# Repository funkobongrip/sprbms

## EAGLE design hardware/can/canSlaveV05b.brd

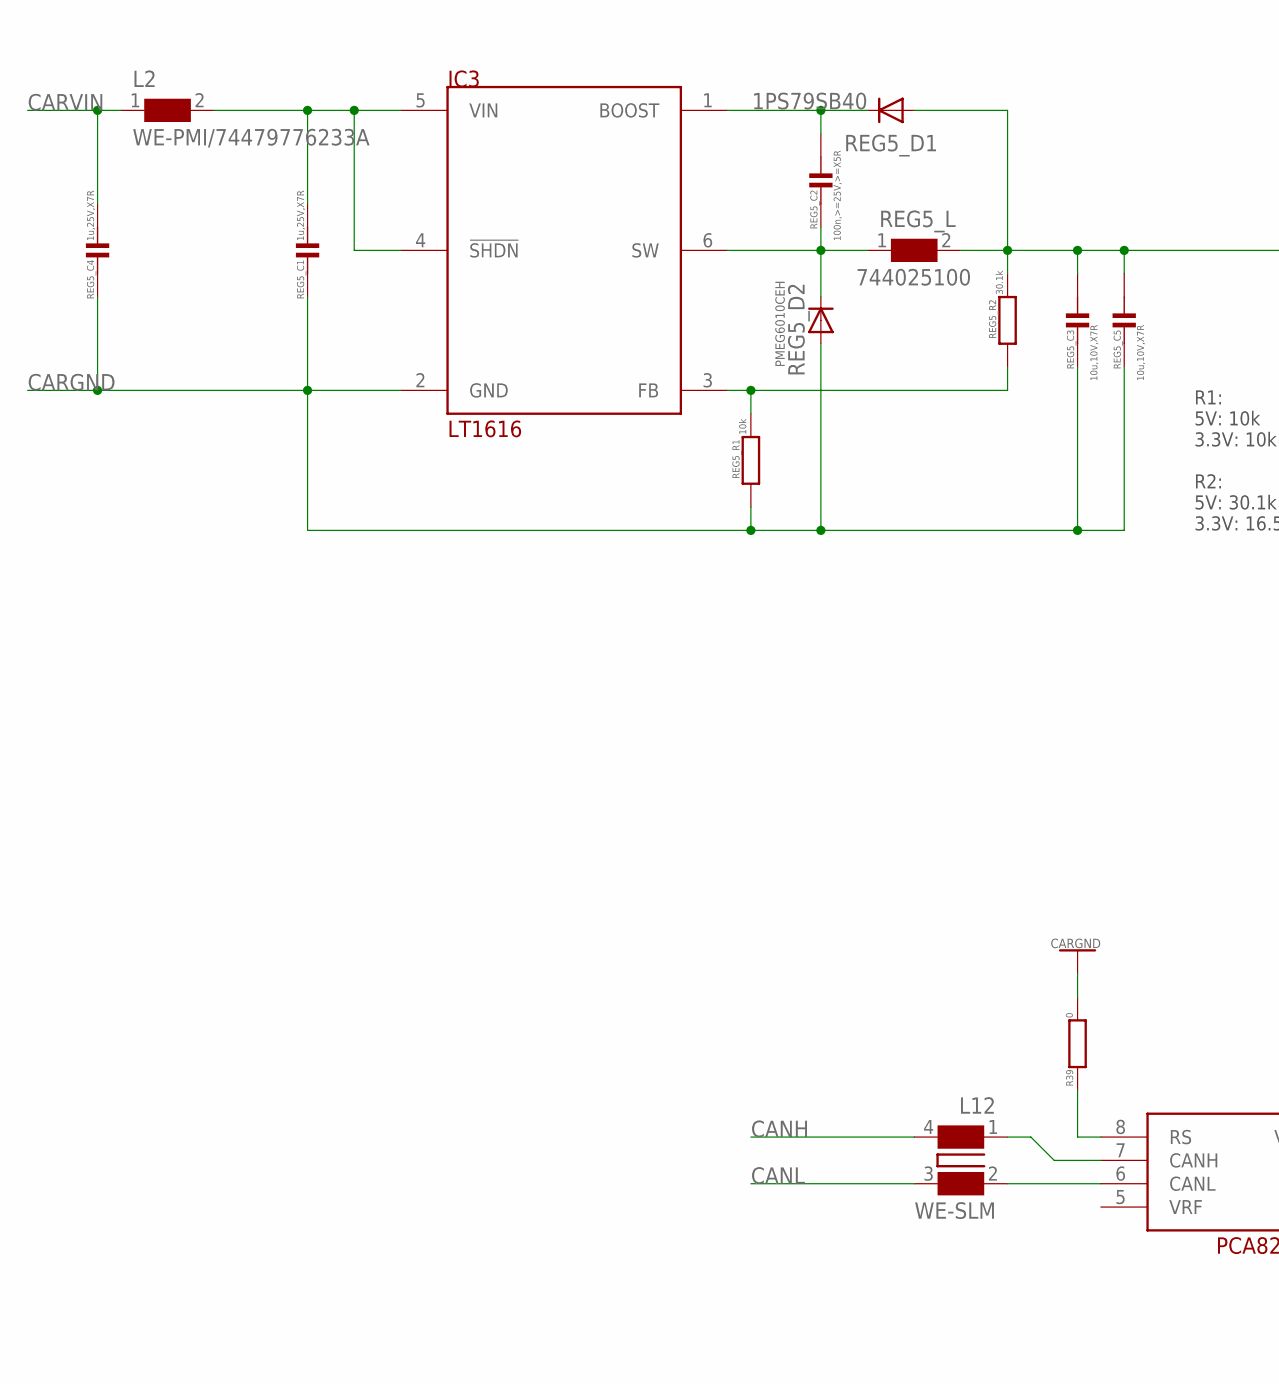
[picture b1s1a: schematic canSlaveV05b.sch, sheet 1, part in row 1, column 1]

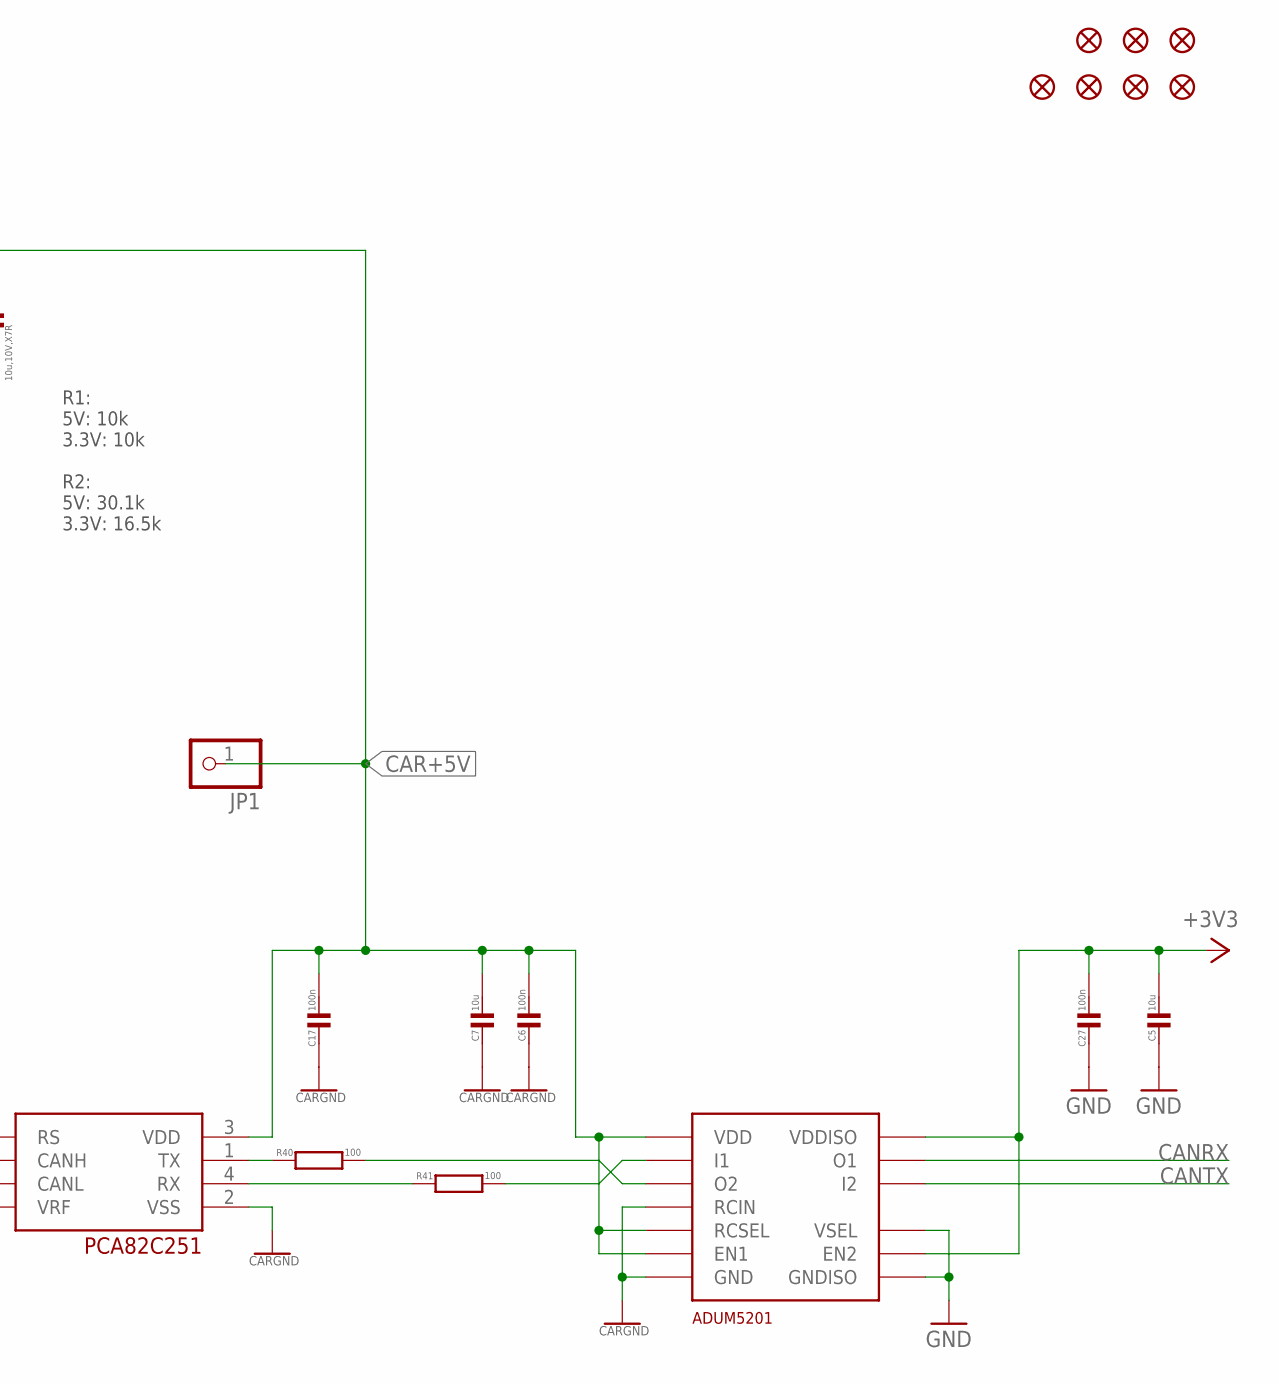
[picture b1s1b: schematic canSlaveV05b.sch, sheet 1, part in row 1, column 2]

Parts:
C5, C7: 10u; C0603
C6, C17, C27: 100n; C0402
FID2, FID3, FID4, FID7, FID8, FID9, FID10: FIDUCIAL""; FIDUCIAL_1MM
IC3: LT1616; SOT23-6
IC5: PCA82C251; SO-8
JP1: PINHD-1X1; 1X01
L2: WE-PMI/74479776233A; WE-PMI_0806
L12: WE-SLM
R39: 0; R0402
R40, R41: 100; R0402
REG5_C1, REG5_C4: 1u,25V,X7R; C0805
REG5_C2: 100n,>=25V,>=X5R; C0402
REG5_C3, REG5_C5: 10u,10V,X7R; C0805
REG5_D1: 1PS79SB40; SOD523
REG5_D2: PMEG6010CEH; SOD123
REG5_L: 744025100; WE-TPC_2828
REG5_R1: 10k; R0402
REG5_R2: 30.1k; R0402
U$2: ADUM5201; SO16WB

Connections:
+3V3: C5.1, C27.1, U$2.P$10 (EN2), U$2.P$16 (VDDISO); also elsewhere on the board
BOOST1: IC3.1 (BOOST), REG5_C2.1, REG5_D1.C
CANH: L12.4; also elsewhere on the board
CANL: L12.3 (2); also elsewhere on the board
CANRX: U$2.P$14 (O1); also elsewhere on the board
CANTX: U$2.P$13 (I2); also elsewhere on the board
CAR+5V: C6.1, C7.1, C17.1, IC5.3 (VDD), JP1.1, REG5_C3.1, REG5_C5.1, REG5_D1.A, REG5_L.2, REG5_R2.2, U$2.P$1 (VDD), U$2.P$6 (RCSEL), U$2.P$7 (EN1)
CARGND: C6.2, C7.2, C17.2, IC3.2 (GND), IC5.2 (VSS), R39.2, REG5_C1.2, REG5_C3.2, REG5_C4.2, REG5_C5.2, REG5_D2.2 (A), REG5_R1.1, U$2.P$2 (GND), U$2.P$5 (RCIN), U$2.P$8 (GND); also elsewhere on the board
CARVIN: L2.1, REG5_C4.1; also elsewhere on the board
CARVINFILT: IC3.4 (!SHDN), IC3.5 (VIN), L2.2, REG5_C1.1
CAR_CANRX: R41.2, U$2.P$3 (I1)
CAR_CANRX_T: IC5.4 (RX), R41.1
CAR_CANTX: R40.2, U$2.P$4 (O2)
CAR_CANTX_T: IC5.1 (TX), R40.1
FB1: IC3.3 (FB), REG5_R1.2, REG5_R2.1
GND: C5.2, C27.2, U$2.P$9 (GNDISO), U$2.P$11 (VSEL), U$2.P$15 (GNDISO); also elsewhere on the board
unnamed: IC5.7 (CANH), L12.1 (3)
unnamed: IC5.6 (CANL), L12.2 (1)
RS1: IC5.8 (RS), R39.1
SW1: IC3.6 (SW), REG5_C2.2, REG5_D2.1 (C), REG5_L.1

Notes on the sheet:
R1: 5V: 10k 3.3V: 10k R2: 5V: 30.1k 3.3V: 16.5k

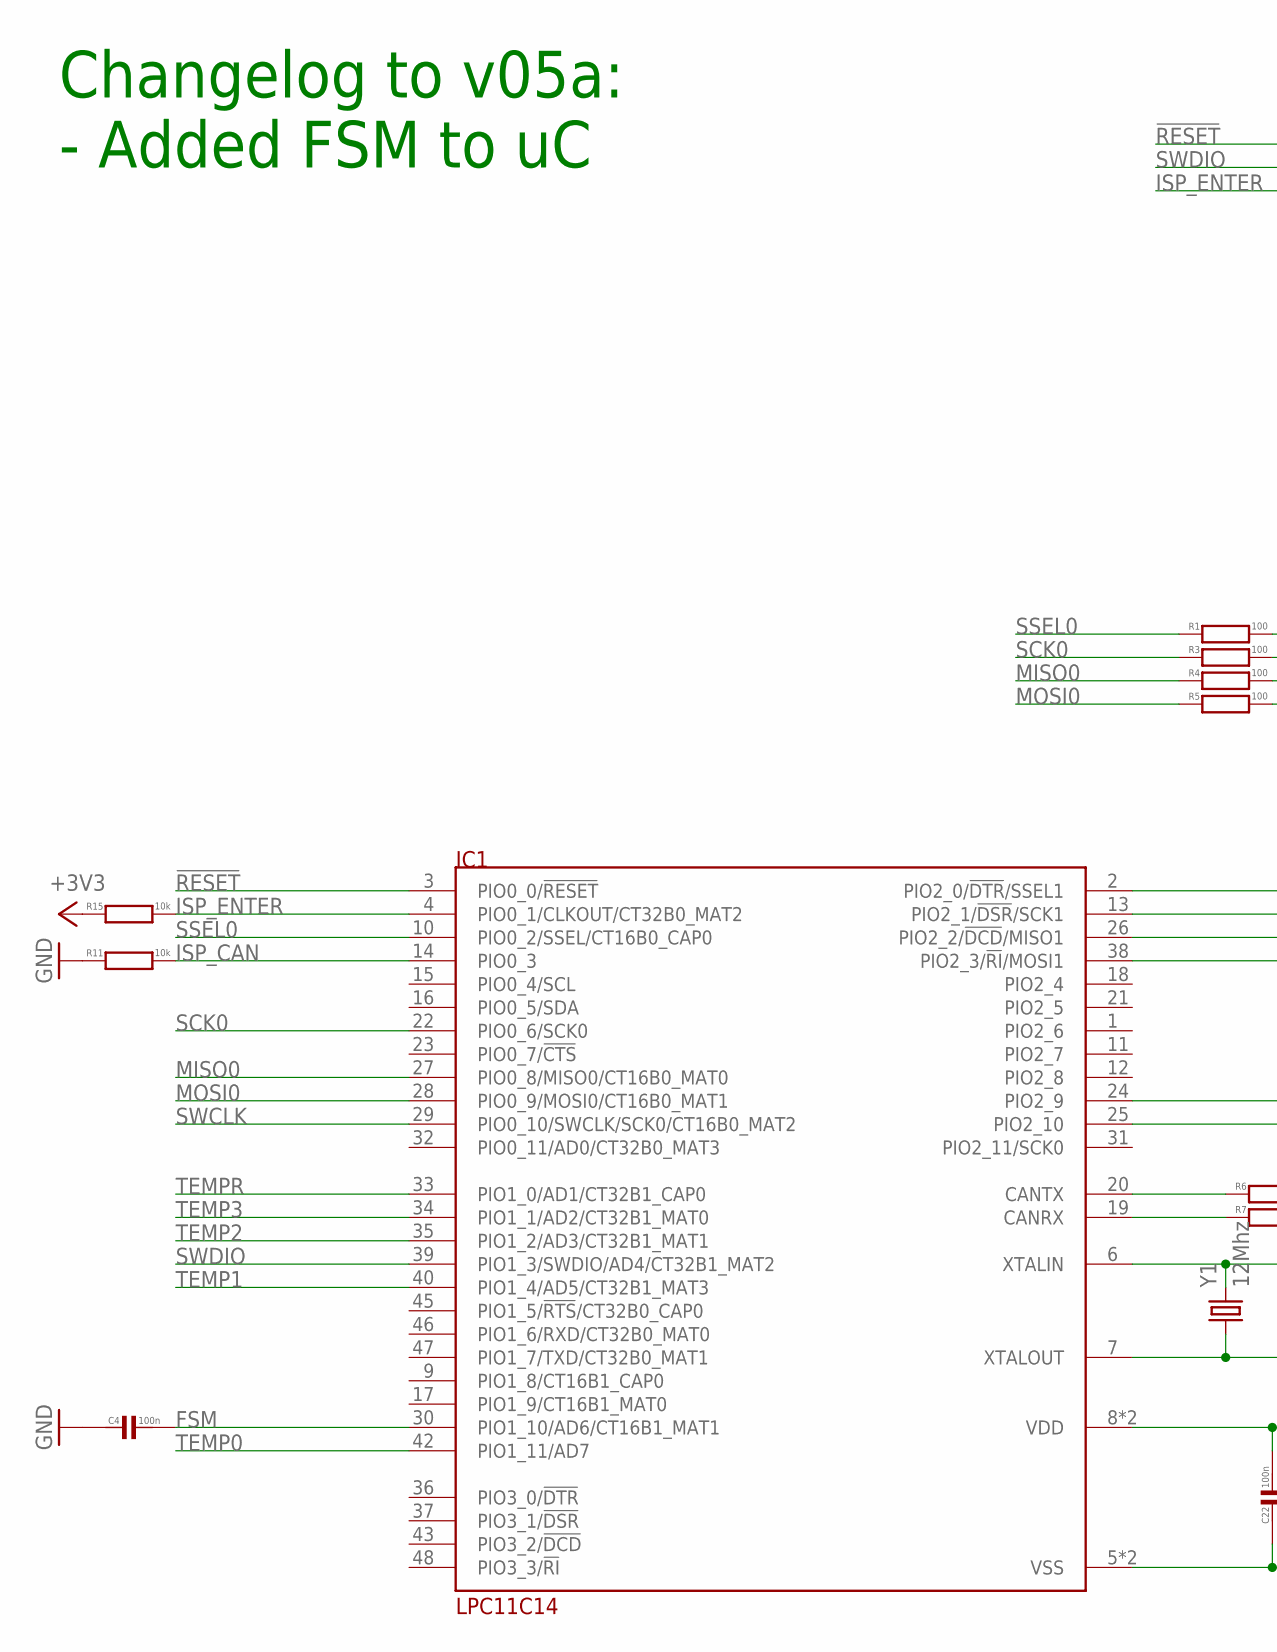
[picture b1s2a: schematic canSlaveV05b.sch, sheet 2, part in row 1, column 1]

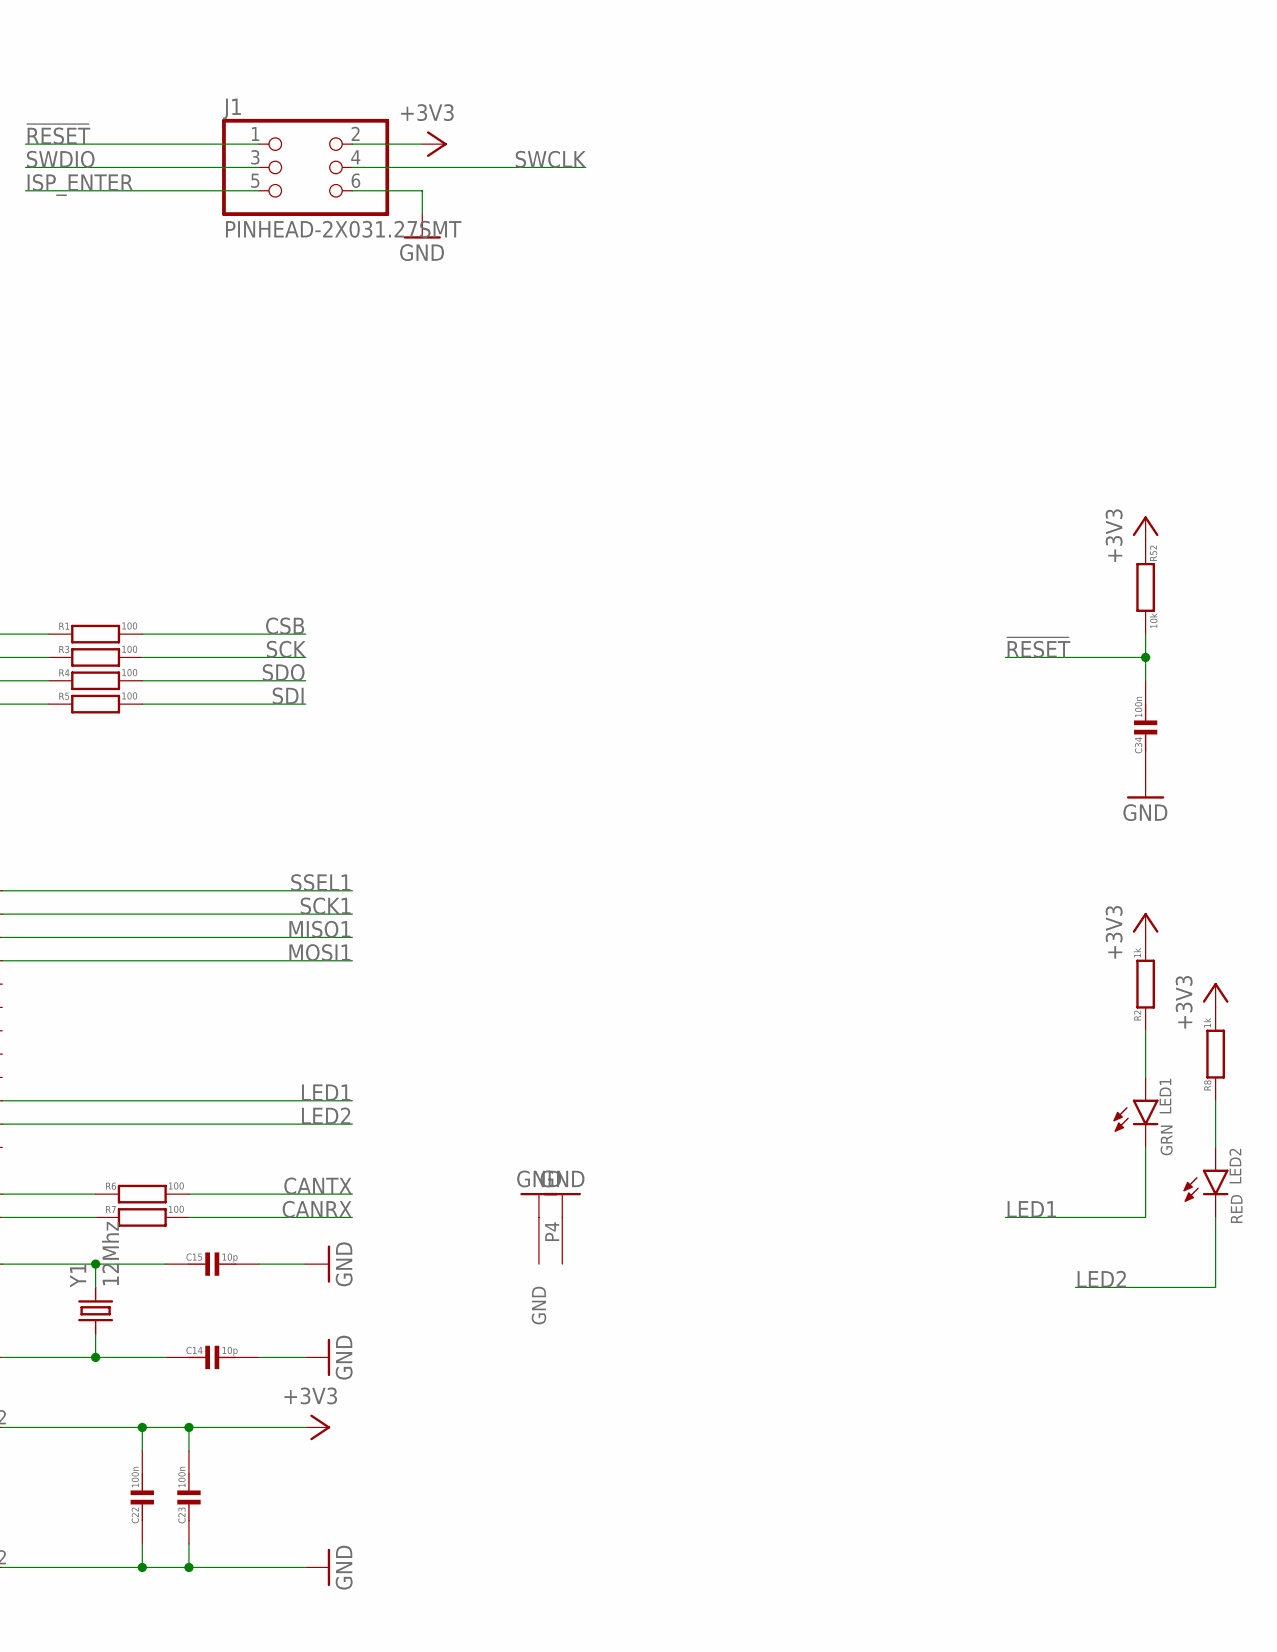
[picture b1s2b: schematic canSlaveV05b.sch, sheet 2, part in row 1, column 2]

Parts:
C4, C22, C23, C34: 100n; C0402
C14, C15: 10p; C0402
IC1: LPC11C14; LQFP48
J1: PINHEAD-2X031.27SMT; 2X03_1.27MM_SMT
LED1: GRN; CHIPLED_0603
LED2: RED; CHIPLED_0603
R1, R3, R4, R5, R6, R7: 100; R0402
R2, R8: 1k; R0402
R11, R15, R52: 10k; R0402
Y1: 12Mhz; MT

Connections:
!RESET: C34.1, IC1.3 (PIO0_0/!RESET), J1.1, R52.2
+3V3: C22.1, C23.1, IC1.8 (VDD), IC1.44 (VDD), J1.2, R2.2, R8.2, R15.1, R52.1; also elsewhere on the board
CANRX: R7.2; also elsewhere on the board
CANRX_U_L: IC1.19 (CANRX), R7.1
CANTX: R6.2; also elsewhere on the board
CANTX_U_L: IC1.20 (CANTX), R6.1
CSB: R1.2; also elsewhere on the board
FSM: C4.1, IC1.30 (PIO1_10/AD6/CT16B1_MAT1); also elsewhere on the board
GND: C4.2, C14.1, C15.1, C22.2, C23.2, C34.2, IC1.5 (VSS), IC1.41 (VSS), J1.6, R11.1, Y1.P2 (GND), Y1.P4 (GND1); also elsewhere on the board
ISP_CAN: IC1.14 (PIO0_3), R11.2
ISP_ENTER: IC1.4 (PIO0_1/CLKOUT/CT32B0_MAT2), J1.5, R15.2
LED1: IC1.24 (PIO2_9), LED1.C
LED2: IC1.25 (PIO2_10), LED2.C
MISO0: IC1.27 (PIO0_8/MISO0/CT16B0_MAT0), R4.1
MISO1: IC1.26 (PIO2_2/!DCD!/MISO1)
MOSI0: IC1.28 (PIO0_9/MOSI0/CT16B0_MAT1), R5.1
MOSI1: IC1.38 (PIO2_3/!RI!/MOSI1)
unnamed: LED2.A, R8.1
unnamed: LED1.A, R2.1
SCK: R3.2; also elsewhere on the board
SCK0: IC1.22 (PIO0_6/SCK0), R3.1
SCK1: IC1.13 (PIO2_1/!DSR!/SCK1)
SDI: R5.2; also elsewhere on the board
SDO: R4.2; also elsewhere on the board
SSEL0: IC1.10 (PIO0_2/SSEL/CT16B0_CAP0), R1.1
SSEL1: IC1.2 (PIO2_0/!DTR!/SSEL1)
SWCLK: IC1.29 (PIO0_10/SWCLK/SCK0/CT16B0_MAT2), J1.4
SWDIO: IC1.39 (PIO1_3/SWDIO/AD4/CT32B1_MAT2), J1.3
TEMP0: IC1.42 (PIO1_11/AD7); also elsewhere on the board
TEMP1: IC1.40 (PIO1_4/AD5/CT32B1_MAT3); also elsewhere on the board
TEMP2: IC1.35 (PIO1_2/AD3/CT32B1_MAT1); also elsewhere on the board
TEMP3: IC1.34 (PIO1_1/AD2/CT32B1_MAT0); also elsewhere on the board
TEMPR: IC1.33 (PIO1_0/AD1/CT32B1_CAP0); also elsewhere on the board
XTALIN: C15.2, IC1.6 (XTALIN), Y1.P3 (2)
XTALOUT: C14.2, IC1.7 (XTALOUT), Y1.P1 (1)

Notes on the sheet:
Changelog to v05a: - Added FSM to uC

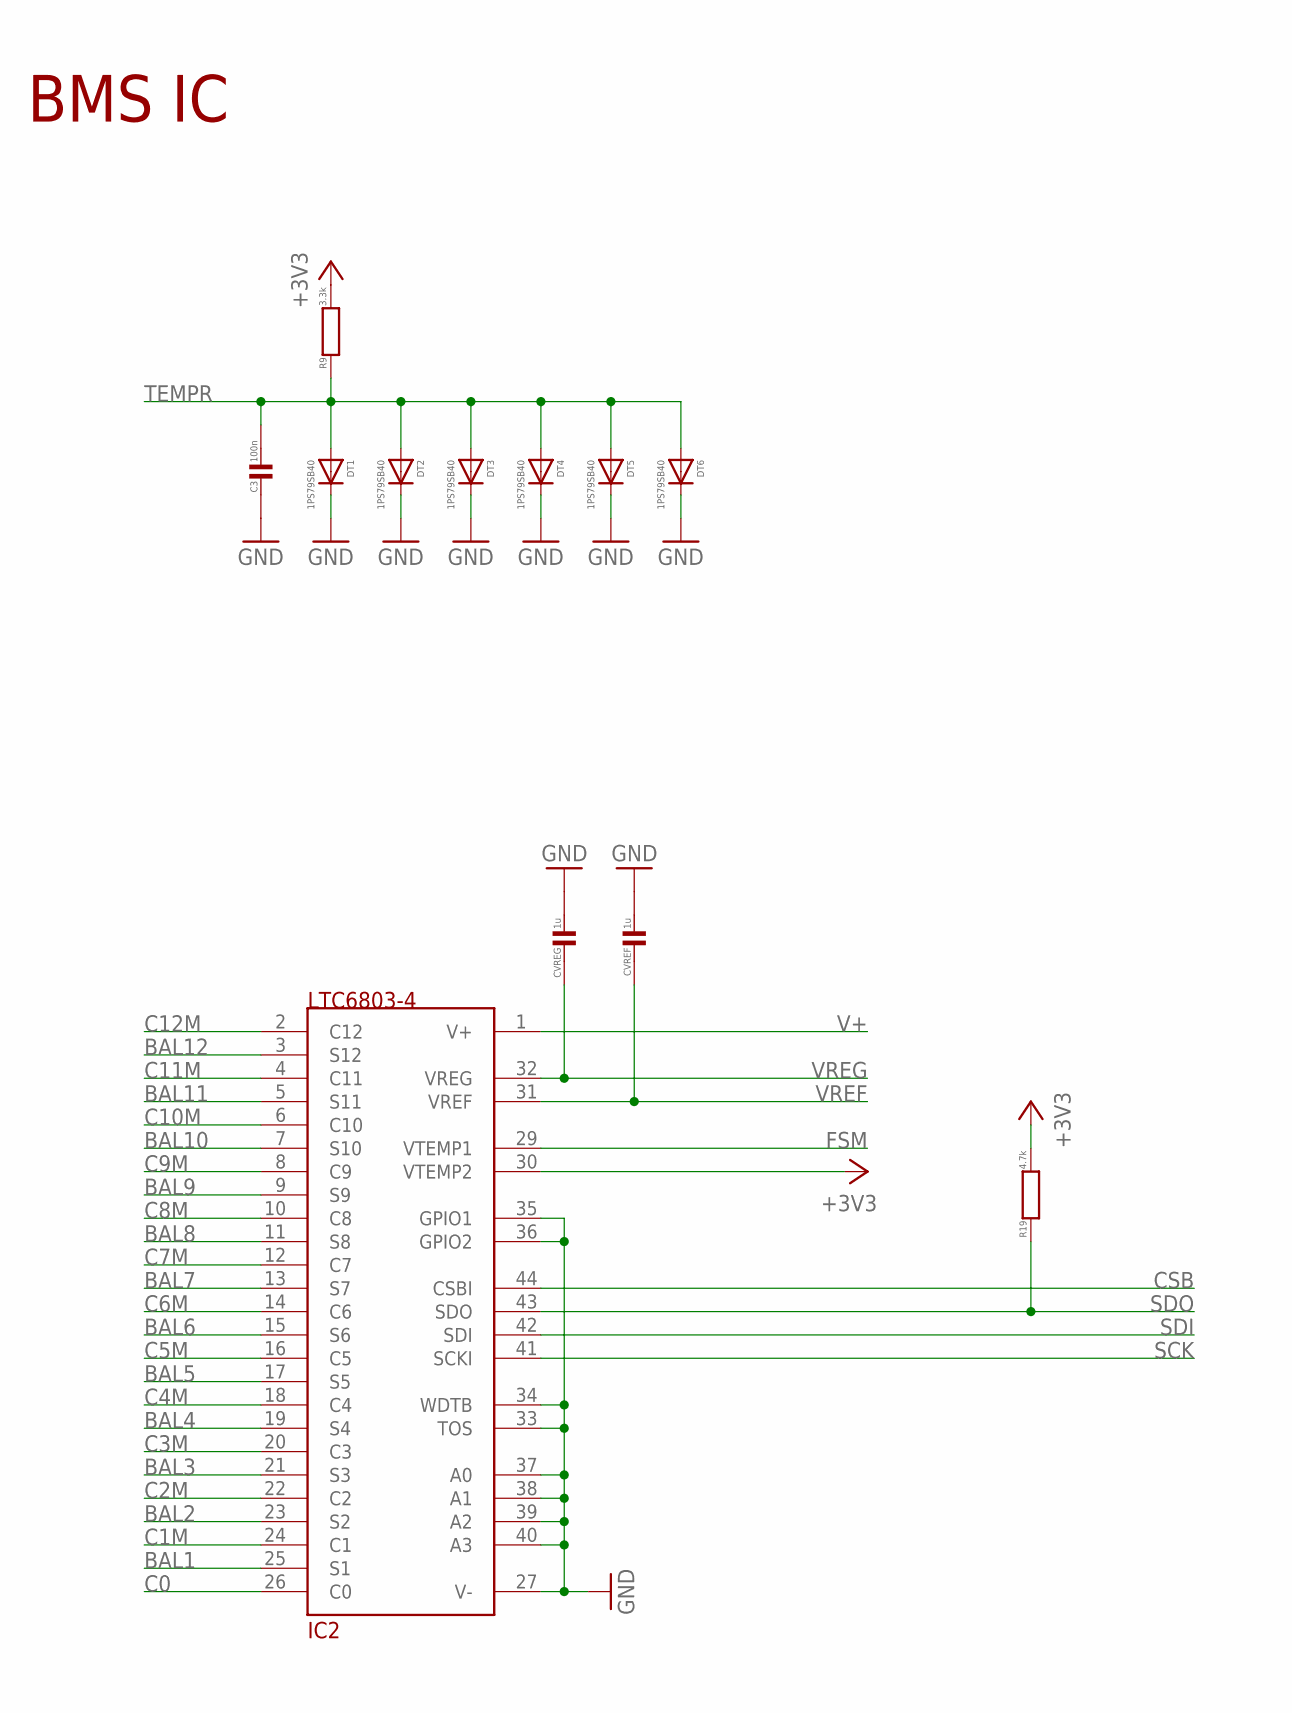
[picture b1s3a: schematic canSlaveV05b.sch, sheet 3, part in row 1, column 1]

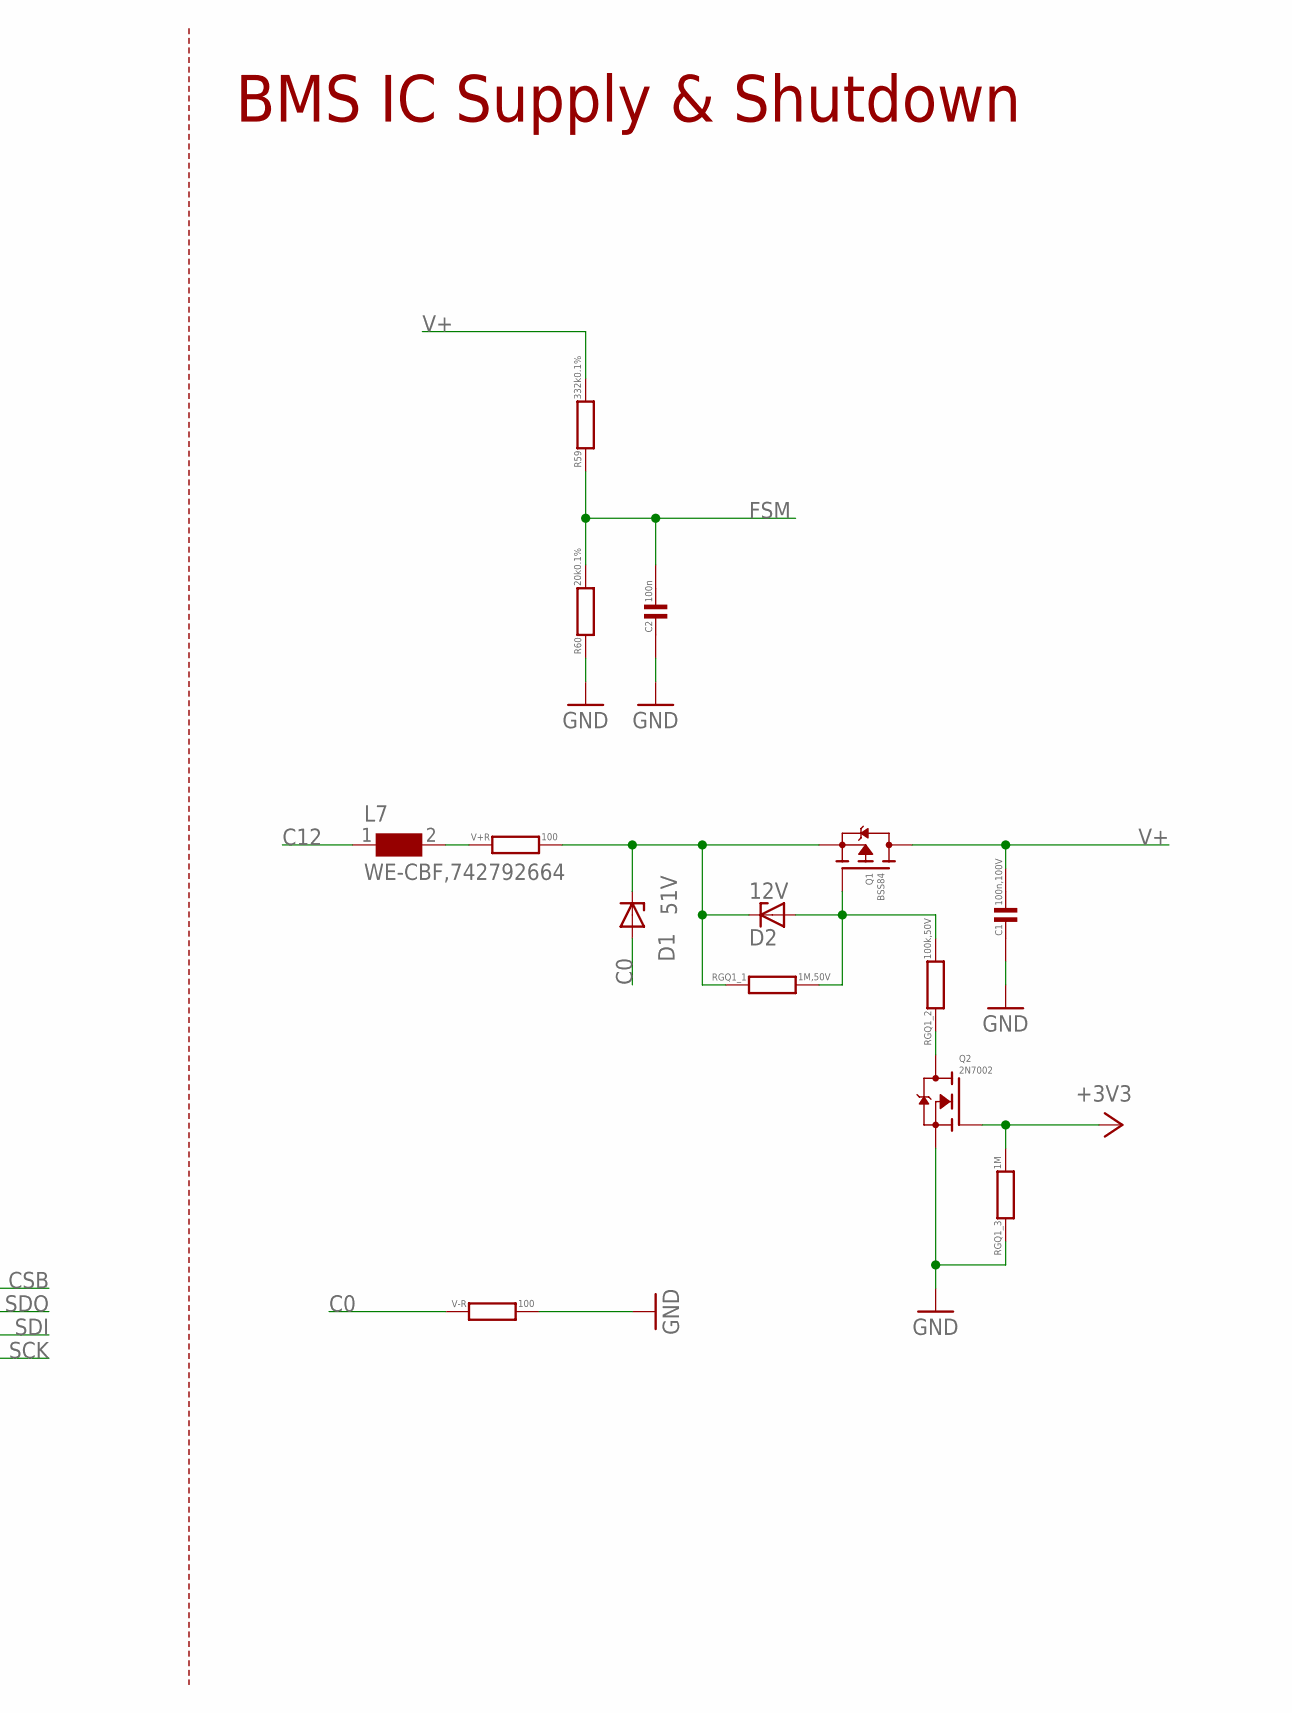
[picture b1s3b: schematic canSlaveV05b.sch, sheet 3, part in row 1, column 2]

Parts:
C1: 100n,100V; C0603
C2, C3: 100n; C0402
CVREF: 1u; C0402
CVREG: 1u; C0402
D1: 51V; SOD323-L
D2: 12V; SOD323-L
DT1, DT2, DT3, DT4, DT5, DT6: 1PS79SB40; SOD523
IC2: LTC6803-4; 44SSOP
L7: WE-CBF,742792664; 0603
Q1: BSS84; SOT23
Q2: 2N7002; SOT23
R9: 3.3k; R0603
R19: 4.7k; R0402
R59: 332k0.1%; R0603
R60: 20k0.1%; R0402
RGQ1_1: 1M,50V; R0603
RGQ1_2: 100k,50V; R0603
RGQ1_3: 1M; R0402
V+R: 100; R0603
V-R: 100; R0603

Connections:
+3V3: IC2.30 (VTEMP2), Q2.1 (G), R9.2, R19.2, RGQ1_3.2; also elsewhere on the board
BAL1: IC2.25 (S1); also elsewhere on the board
BAL2: IC2.23 (S2); also elsewhere on the board
BAL3: IC2.21 (S3); also elsewhere on the board
BAL4: IC2.19 (S4); also elsewhere on the board
BAL5: IC2.17 (S5); also elsewhere on the board
BAL6: IC2.15 (S6); also elsewhere on the board
BAL7: IC2.13 (S7); also elsewhere on the board
BAL8: IC2.11 (S8); also elsewhere on the board
BAL9: IC2.9 (S9); also elsewhere on the board
BAL10: IC2.7 (S10); also elsewhere on the board
BAL11: IC2.5 (S11); also elsewhere on the board
BAL12: IC2.3 (S12); also elsewhere on the board
C0: D1.A, IC2.26 (C0), V-R.1; also elsewhere on the board
C1M: IC2.24 (C1); also elsewhere on the board
C2M: IC2.22 (C2); also elsewhere on the board
C3M: IC2.20 (C3); also elsewhere on the board
C4M: IC2.18 (C4); also elsewhere on the board
C5M: IC2.16 (C5); also elsewhere on the board
C6M: IC2.14 (C6); also elsewhere on the board
C7M: IC2.12 (C7); also elsewhere on the board
C8M: IC2.10 (C8); also elsewhere on the board
C9M: IC2.8 (C9); also elsewhere on the board
C10M: IC2.6 (C10); also elsewhere on the board
C11M: IC2.4 (C11); also elsewhere on the board
C12: L7.1; also elsewhere on the board
C12M: IC2.2 (C12); also elsewhere on the board
CSB: IC2.44 (CSBI); also elsewhere on the board
FSM: C2.1, IC2.29 (VTEMP1), R59.1, R60.2; also elsewhere on the board
GND: C1.2, C2.2, C3.2, CVREF.1, CVREG.1, DT1.C, DT2.C, DT3.C, DT4.C, DT5.C, DT6.C, IC2.27 (V-), IC2.33 (TOS), IC2.34 (WDTB), IC2.35 (GPIO1), IC2.36 (GPIO2), IC2.37 (A0), IC2.38 (A1), IC2.39 (A2), IC2.40 (A3), Q2.2 (S), R60.1, RGQ1_3.1, V-R.2; also elsewhere on the board
unnamed: Q2.3 (D), RGQ1_2.1
unnamed: L7.2, V+R.1
Q1G: D2.A, Q1.1 (G), RGQ1_1.2, RGQ1_2.2
SCK: IC2.41 (SCKI); also elsewhere on the board
SDI: IC2.42 (SDI); also elsewhere on the board
SDO: IC2.43 (SDO), R19.1; also elsewhere on the board
TEMPR: C3.1, DT1.A, DT2.A, DT3.A, DT4.A, DT5.A, DT6.A, R9.1; also elsewhere on the board
V+: C1.1, IC2.1 (V+), Q1.3 (D), R59.2
V+S: D1.C, D2.C, Q1.2 (S), RGQ1_1.1, V+R.2
VREF: CVREF.2, IC2.31 (VREF)
VREG: CVREG.2, IC2.32 (VREG)

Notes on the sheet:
BMS IC
BMS IC Supply & Shutdown

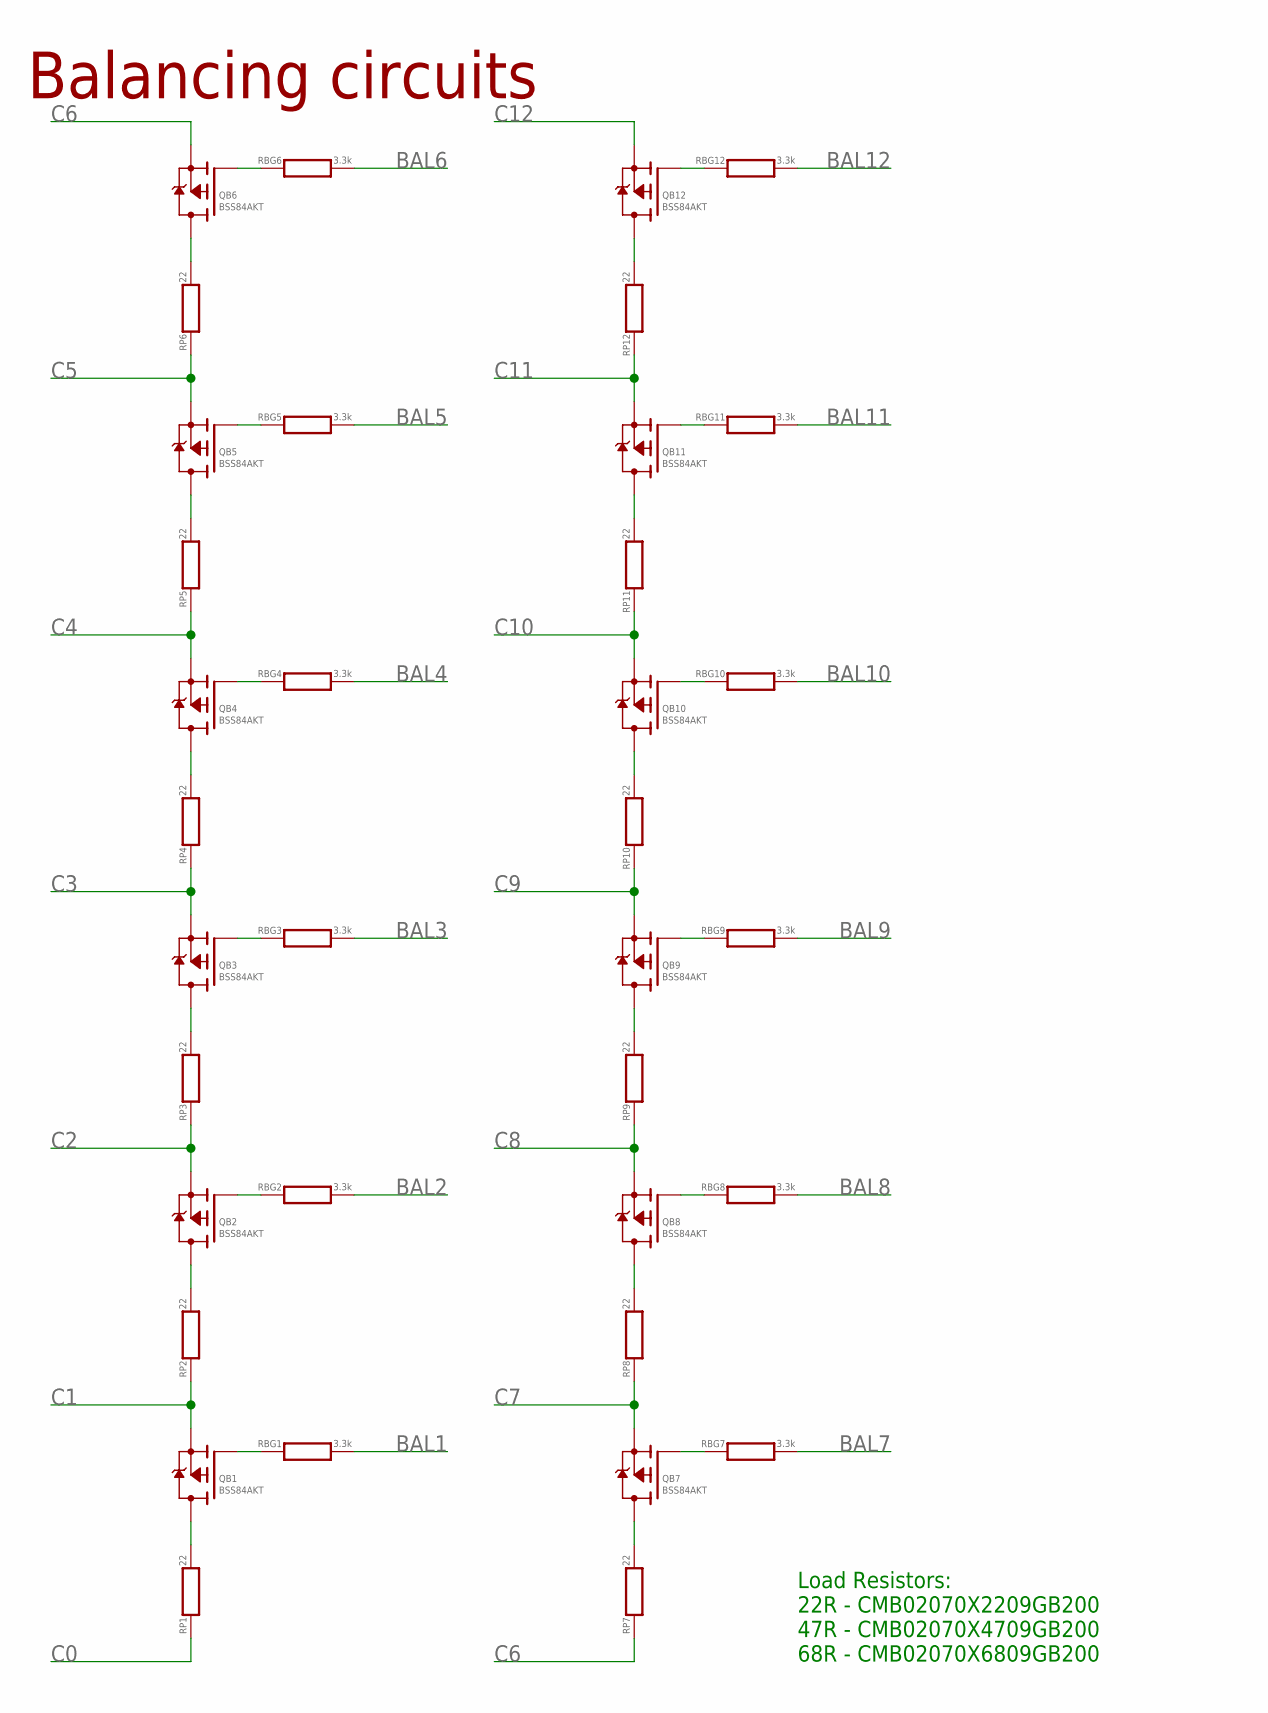
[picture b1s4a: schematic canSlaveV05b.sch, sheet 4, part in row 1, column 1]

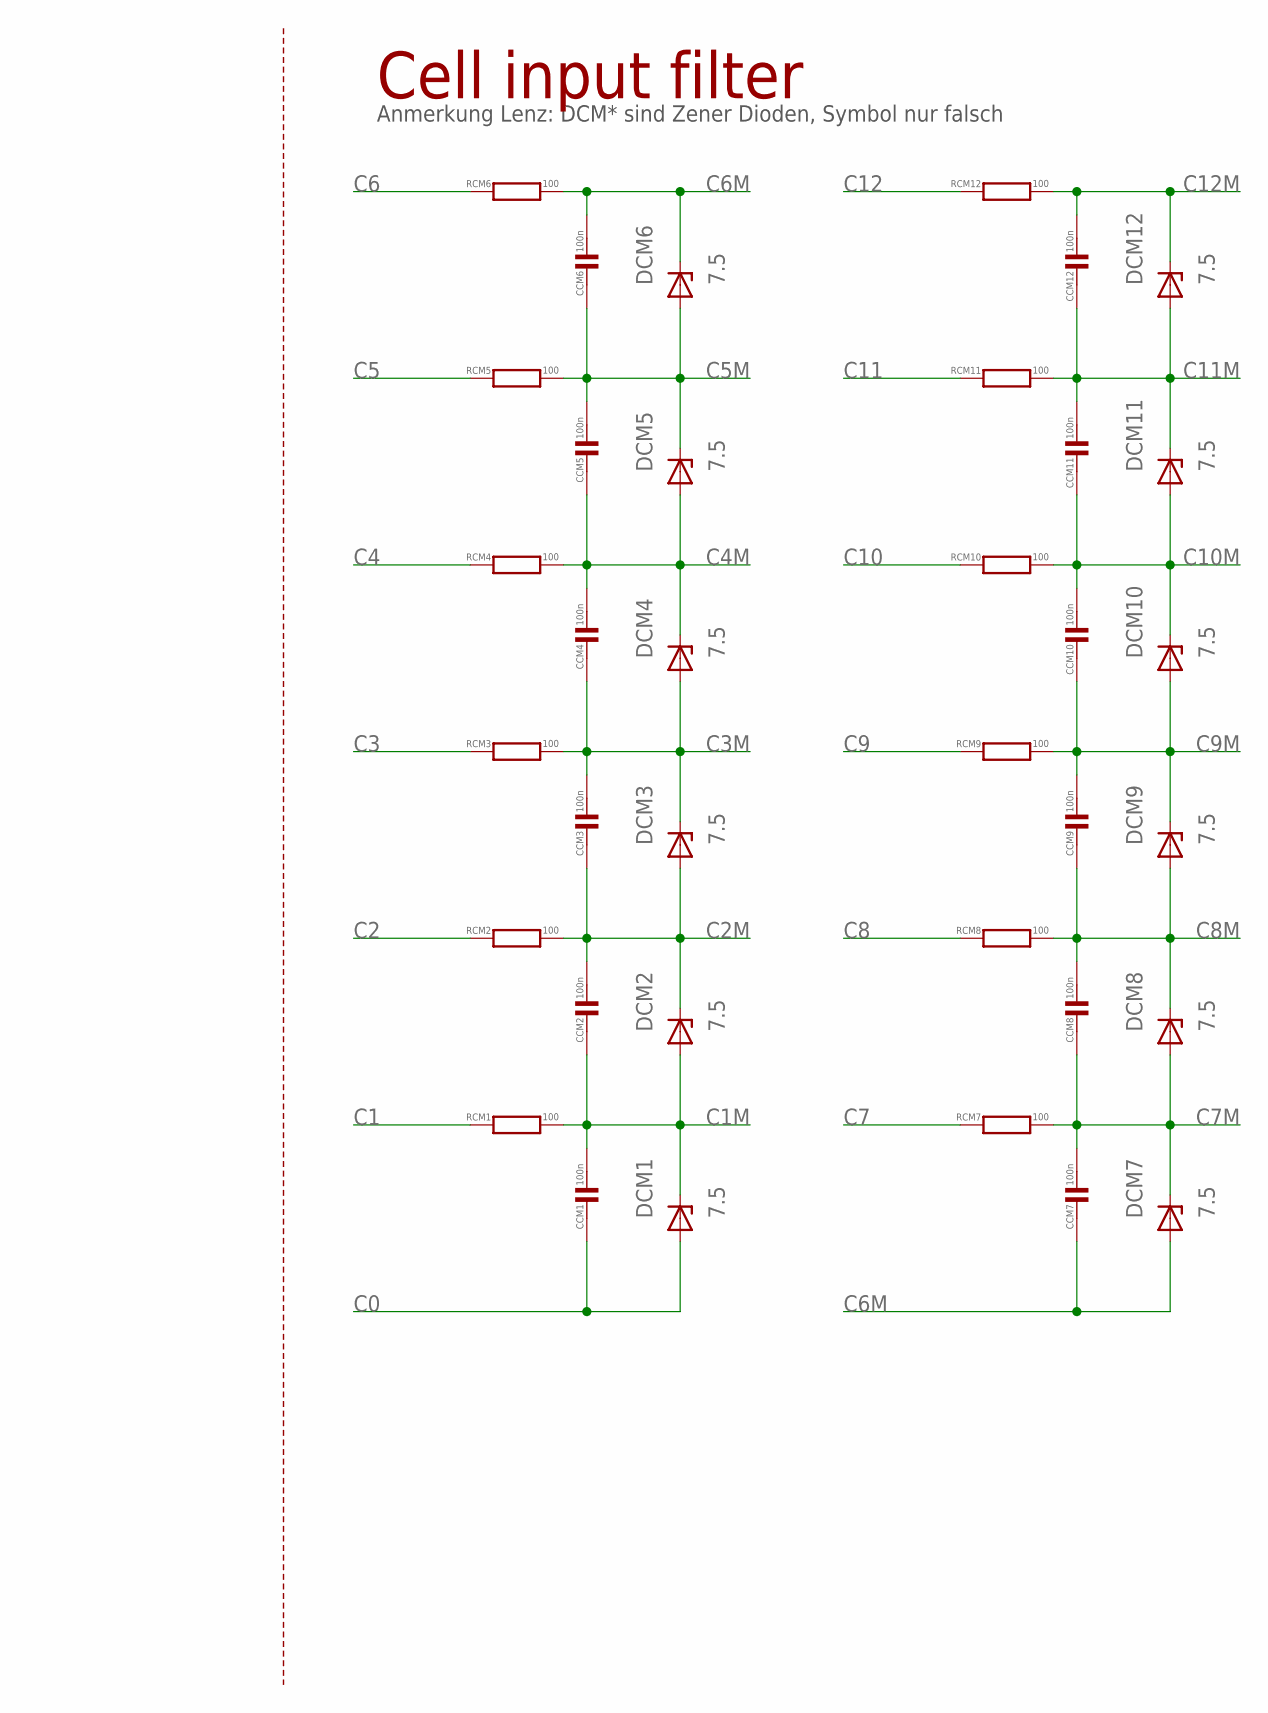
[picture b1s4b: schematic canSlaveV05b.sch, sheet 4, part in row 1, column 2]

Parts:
CCM1, CCM2, CCM3, CCM4, CCM5, CCM6, CCM7, CCM8, CCM9, CCM10, CCM11, CCM12: 100n; C0402
DCM1, DCM2, DCM3, DCM4, DCM5, DCM6, DCM7, DCM8, DCM9, DCM10, DCM11, DCM12: 7.5; SOD523
QB1, QB2, QB3, QB4, QB5, QB6, QB7, QB8, QB9, QB10, QB11, QB12: BSS84AKT; SOT416
RBG1, RBG2, RBG3, RBG4, RBG5, RBG6, RBG7, RBG8, RBG9, RBG10, RBG11, RBG12: 3.3k; R0402
RCM1, RCM2, RCM3, RCM4, RCM5, RCM6, RCM7, RCM8, RCM9, RCM10, RCM11, RCM12: 100; R0402
RP1, RP2, RP3, RP4, RP5, RP6, RP7, RP8, RP9, RP10, RP11, RP12: 22; MINI_MELF-0207R

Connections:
BAL1: RBG1.2; also elsewhere on the board
BAL2: RBG2.2; also elsewhere on the board
BAL3: RBG3.2; also elsewhere on the board
BAL4: RBG4.2; also elsewhere on the board
BAL5: RBG5.2; also elsewhere on the board
BAL6: RBG6.2; also elsewhere on the board
BAL7: RBG7.2; also elsewhere on the board
BAL8: RBG8.2; also elsewhere on the board
BAL9: RBG9.2; also elsewhere on the board
BAL10: RBG10.2; also elsewhere on the board
BAL11: RBG11.2; also elsewhere on the board
BAL12: RBG12.2; also elsewhere on the board
C0: CCM1.2, DCM1.A, RP1.1; also elsewhere on the board
C1: QB1.2 (S), RCM1.1, RP2.1; also elsewhere on the board
C1M: CCM1.1, CCM2.2, DCM1.C, DCM2.A, RCM1.2; also elsewhere on the board
C2: QB2.2 (S), RCM2.1, RP3.1; also elsewhere on the board
C2M: CCM2.1, CCM3.2, DCM2.C, DCM3.A, RCM2.2; also elsewhere on the board
C3: QB3.2 (S), RCM3.1, RP4.1; also elsewhere on the board
C3M: CCM3.1, CCM4.2, DCM3.C, DCM4.A, RCM3.2; also elsewhere on the board
C4: QB4.2 (S), RCM4.1, RP5.1; also elsewhere on the board
C4M: CCM4.1, CCM5.2, DCM4.C, DCM5.A, RCM4.2; also elsewhere on the board
C5: QB5.2 (S), RCM5.1, RP6.1; also elsewhere on the board
C5M: CCM5.1, CCM6.2, DCM5.C, DCM6.A, RCM5.2; also elsewhere on the board
C6: QB6.2 (S), RCM6.1, RP7.1; also elsewhere on the board
C6M: CCM6.1, CCM7.2, DCM6.C, DCM7.A, RCM6.2; also elsewhere on the board
C7: QB7.2 (S), RCM7.1, RP8.1; also elsewhere on the board
C7M: CCM7.1, CCM8.2, DCM7.C, DCM8.A, RCM7.2; also elsewhere on the board
C8: QB8.2 (S), RCM8.1, RP9.1; also elsewhere on the board
C8M: CCM8.1, CCM9.2, DCM8.C, DCM9.A, RCM8.2; also elsewhere on the board
C9: QB9.2 (S), RCM9.1, RP10.1; also elsewhere on the board
C9M: CCM9.1, CCM10.2, DCM9.C, DCM10.A, RCM9.2; also elsewhere on the board
C10: QB10.2 (S), RCM10.1, RP11.1; also elsewhere on the board
C10M: CCM10.1, CCM11.2, DCM10.C, DCM11.A, RCM10.2; also elsewhere on the board
C11: QB11.2 (S), RCM11.1, RP12.1; also elsewhere on the board
C11M: CCM11.1, CCM12.2, DCM11.C, DCM12.A, RCM11.2; also elsewhere on the board
C12: QB12.2 (S), RCM12.1; also elsewhere on the board
C12M: CCM12.1, DCM12.C, RCM12.2; also elsewhere on the board
CR1: QB1.3 (D), RP1.2
CR2: QB2.3 (D), RP2.2
CR3: QB3.3 (D), RP3.2
CR4: QB4.3 (D), RP4.2
CR5: QB5.3 (D), RP5.2
CR6: QB6.3 (D), RP6.2
CR7: QB7.3 (D), RP7.2
CR8: QB8.3 (D), RP8.2
CR9: QB9.3 (D), RP9.2
CR10: QB10.3 (D), RP10.2
CR11: QB11.3 (D), RP11.2
CR12: QB12.3 (D), RP12.2
QBG1: QB1.1 (G), RBG1.1
QBG2: QB2.1 (G), RBG2.1
QBG3: QB3.1 (G), RBG3.1
QBG4: QB4.1 (G), RBG4.1
QBG5: QB5.1 (G), RBG5.1
QBG6: QB6.1 (G), RBG6.1
QBG7: QB7.1 (G), RBG7.1
QBG8: QB8.1 (G), RBG8.1
QBG9: QB9.1 (G), RBG9.1
QBG10: QB10.1 (G), RBG10.1
QBG11: QB11.1 (G), RBG11.1
QBG12: QB12.1 (G), RBG12.1

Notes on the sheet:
Balancing circuits
Cell input filter
Anmerkung Lenz: DCM* sind Zener Dioden, Symbol nur falsch
Load Resistors: 22R - CMB02070X2209GB200 47R - CMB02070X4709GB200 68R - CMB02070X6809GB200

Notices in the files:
hardware/can/canSlaveV04 Flach.brd:
canSlaveV04 - CC BY-NC-SA 2.0
hardware/can/canSlaveV05b.brd:
CC BY-NC-SA
parts and their libraries:
microbuilder: This work is placed in the public domain, and may be freely used for commercial and non-commercial work with the following conditions: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
EagleLibrary_Wuerth_Elektronik_eiSos_Ver: Copyright: Würth Elektronik
